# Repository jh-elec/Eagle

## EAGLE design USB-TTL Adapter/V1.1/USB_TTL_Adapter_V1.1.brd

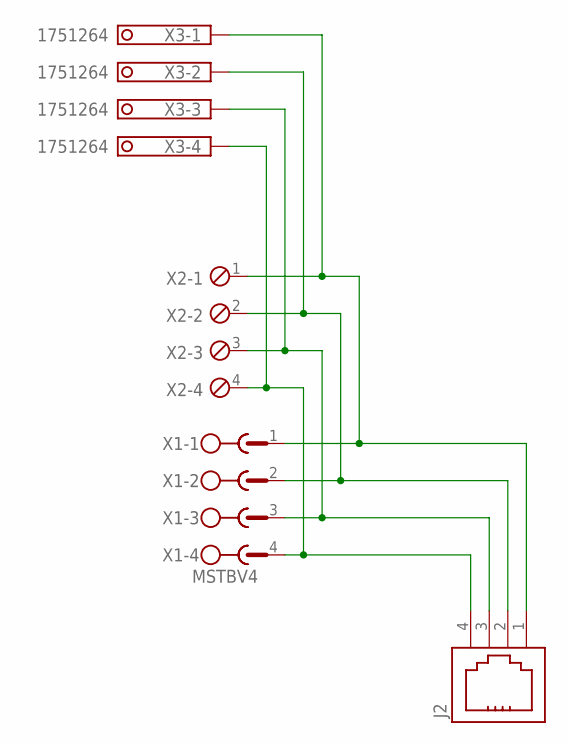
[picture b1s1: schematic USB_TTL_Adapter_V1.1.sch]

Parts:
J2: 615004144021
X1: MSTBV4
X2: MPT4; 4POL254
X3: 1751264

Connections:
unnamed: J2.4, X1.4, X2.4, X3.4
unnamed: J2.3, X1.3, X2.3, X3.3
unnamed: J2.2, X1.2, X2.2, X3.2
unnamed: J2.1, X1.1, X2.1, X3.1

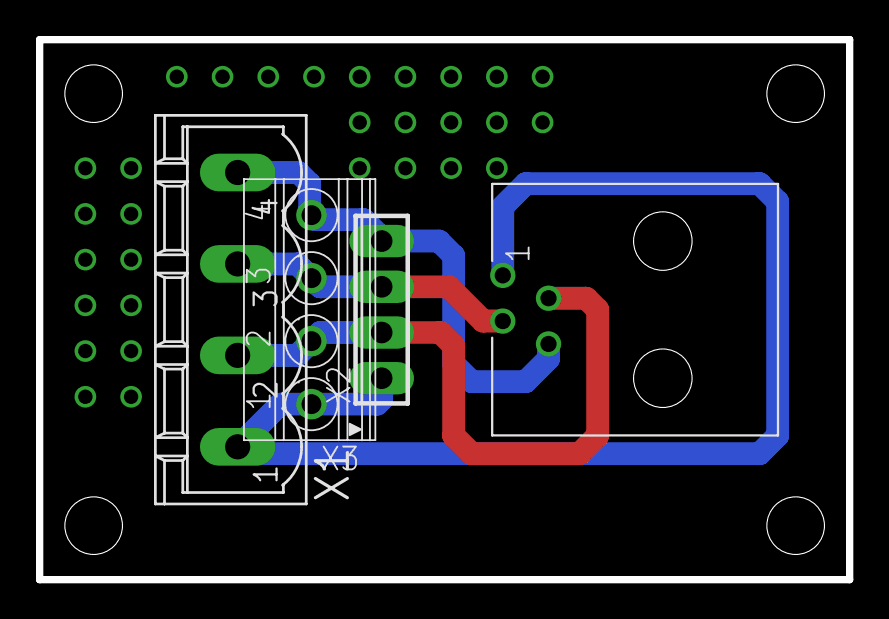
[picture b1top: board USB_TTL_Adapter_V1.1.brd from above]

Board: 2 copper layers, 45.0 x 30.0 mm, 5 parts (0 on the bottom side), 4 nets.

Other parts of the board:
U$1: 25X25_BEST

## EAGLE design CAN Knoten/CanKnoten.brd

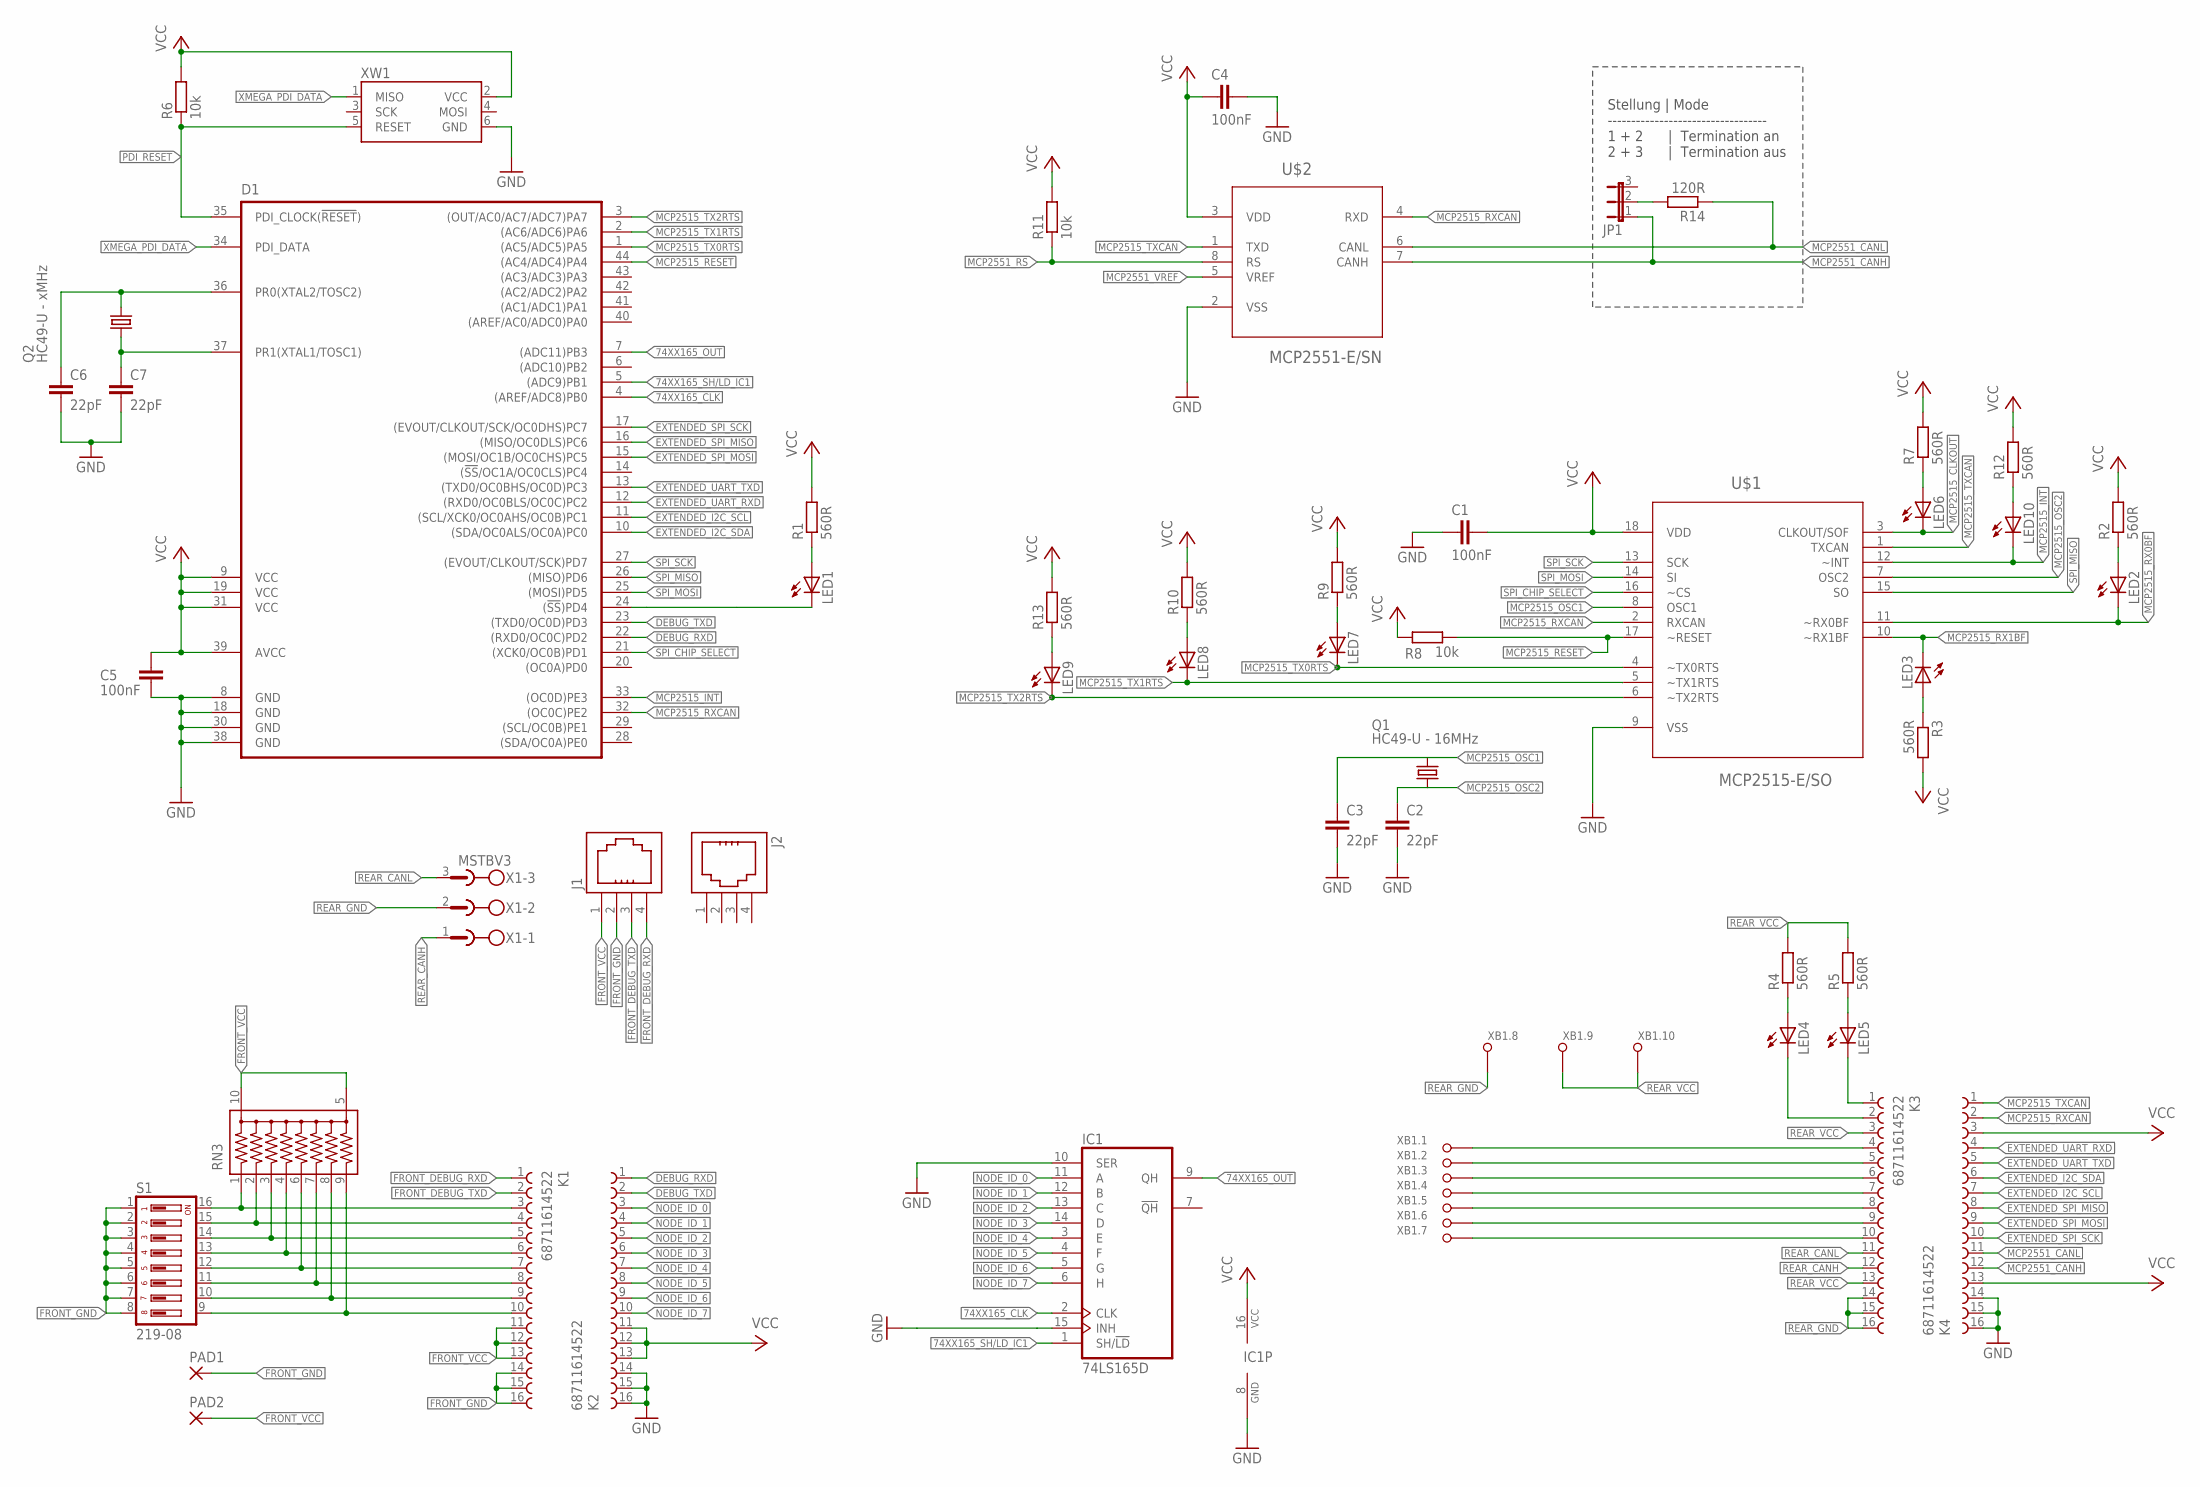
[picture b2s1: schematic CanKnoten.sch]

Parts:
C1, C4, C5: 100nF; C1206
C2, C3, C6, C7: 22pF; C1206
D1: ATXMEGA16D4/32D4/64D4/128D4-A; TQFP44A
IC1: 74LS165D; SO16
J1: 615004143821
J2: 615004144021
JP1: JP2E; JP2
K1, K2, K3, K4: 68711614522
LED1, LED2, LED3, LED4, LED5, LED6, LED7, LED8, LED9, LED10: LEDSML1206; SML1206
PAD1, PAD2: SMD5; SMD2,54-5,08
Q1: HC49-U - 16MHz; HC49
Q2: HC49-U - xMHz; HC49
R1, R2, R3, R4, R5, R7, R9, R10, R12, R13: 560R; R1206
R6, R8, R11: 10k; R1206
R14: 120R; R1206
RN3: 745-10
S1: 219-08; CTS-219-08
U$1: MCP2515-E/SO; SOIC127P1030X265-18N
U$2: MCP2551-E/SN; SOIC127P600X175-8N
X1: MSTBV3
XB1: WSL10
XW1: WSL6; WSL

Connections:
74XX165_CLK: D1.4 ((AREF/ADC8)PB0), IC1.2 (CLK)
74XX165_OUT: D1.7 ((ADC11)PB3), IC1.9 (QH)
74XX165_SH/LD_IC1: D1.5 ((ADC9)PB1), IC1.1 (SH/!LD)
DEBUG_RXD: D1.22 ((RXD0/OC0C)PD2), K2.1
DEBUG_TXD: D1.23 ((TXD0/OC0D)PD3), K2.2
EXTENDED_I2C_SCL: D1.11 ((SCL/XCK0/OC0AHS/OC0B)PC1), K4.7
EXTENDED_I2C_SDA: D1.10 ((SDA/OC0ALS/OC0A)PC0), K4.6
EXTENDED_SPI_MISO: D1.16 ((MISO/OC0DLS)PC6), K4.8
EXTENDED_SPI_MOSI: D1.15 ((MOSI/OC1B/OC0CHS)PC5), K4.9
EXTENDED_SPI_SCK: D1.17 ((EVOUT/CLKOUT/SCK/OC0DHS)PC7), K4.10
EXTENDED_UART_RXD: D1.12 ((RXD0/OC0BLS/OC0C)PC2), K4.4
EXTENDED_UART_TXD: D1.13 ((TXD0/OC0BHS/OC0D)PC3), K4.5
FRONT_DEBUG_RXD: J1.4 (1), K1.1
FRONT_DEBUG_TXD: J1.3 (2), K1.2
FRONT_GND: J1.2 (3), K1.14, K1.15, K1.16, PAD1.1, S1.1, S1.2, S1.3, S1.4, S1.5, S1.6, S1.7, S1.8
FRONT_VCC: J1.1 (4), K1.11, K1.12, K1.13, PAD2.1, RN3.5, RN3.10
GND: C1.2, C2.2, C3.2, C4.1, C5.2, C6.2, C7.2, D1.8 (GND), D1.18 (GND), D1.30 (GND), D1.38 (GND), IC1.8 (GND), IC1.10 (SER), IC1.15 (INH), K2.14, K2.15, K2.16, K4.14, K4.15, K4.16, U$1.9 (VSS), U$2.2 (VSS), XW1.6 (GND)
MCP2515_CLKOUT: LED6.C, U$1.3 (CLKOUT/SOF)
MCP2515_INT: D1.33 ((OC0D)PE3), LED10.C, U$1.12 (~INT)
MCP2515_OSC1: C3.1, Q1.2, U$1.8 (OSC1)
MCP2515_OSC2: C2.1, Q1.1, U$1.7 (OSC2)
MCP2515_RESET: D1.44 ((AC4/ADC4)PA4), R8.1, U$1.17 (~RESET)
MCP2515_RX0BF: LED2.C, U$1.11 (~RX0BF)
MCP2515_RX1BF: LED3.C, U$1.10 (~RX1BF)
MCP2515_RXCAN: D1.32 ((OC0C)PE2), K4.2, U$1.2 (RXCAN), U$2.4 (RXD)
MCP2515_TX0RTS: D1.1 ((AC5/ADC5)PA5), LED7.C, U$1.4 (~TX0RTS)
MCP2515_TX1RTS: D1.2 ((AC6/ADC6)PA6), LED8.C, U$1.5 (~TX1RTS)
MCP2515_TX2RTS: D1.3 ((OUT/AC0/AC7/ADC7)PA7), LED9.C, U$1.6 (~TX2RTS)
MCP2515_TXCAN: K4.1, U$1.1 (TXCAN), U$2.1 (TXD)
MCP2551_CANH: JP1.1, K4.12, U$2.7 (CANH)
MCP2551_CANL: K4.11, R14.1, U$2.6 (CANL)
MCP2551_RS: R11.1, U$2.8 (RS)
MCP2551_VREF: U$2.5 (VREF)
unnamed: LED2.A, R2.1
unnamed: K3.4, XB1.1
unnamed: LED3.A, R3.1
unnamed: K3.5, XB1.2
unnamed: K3.6, XB1.3
unnamed: K3.7, XB1.4
unnamed: K3.8, XB1.5
unnamed: K3.9, XB1.6
unnamed: K3.10, XB1.7
unnamed: LED10.A, R12.1
unnamed: JP1.2, R14.2
unnamed: LED6.A, R7.1
unnamed: LED7.A, R9.1
unnamed: C6.1, D1.36 (PR0(XTAL2/TOSC2)), Q2.2
unnamed: C7.1, D1.37 (PR1(XTAL1/TOSC1)), Q2.1
unnamed: LED8.A, R10.1
unnamed: LED9.A, R13.1
unnamed: K1.3, RN3.1, S1.16
unnamed: K1.4, RN3.2, S1.15
unnamed: K1.5, RN3.3, S1.14
unnamed: K1.6, RN3.4, S1.13
unnamed: K1.7, RN3.6, S1.12
unnamed: K1.8, RN3.7, S1.11
unnamed: K1.9, RN3.8, S1.10
unnamed: K1.10, RN3.9, S1.9
unnamed: LED1.A, R1.1
unnamed: LED4.A, R4.1
unnamed: LED5.A, R5.1
NODE_ID_0: IC1.11 (A), K2.3
NODE_ID_1: IC1.12 (B), K2.4
NODE_ID_2: IC1.13 (C), K2.5
NODE_ID_3: IC1.14 (D), K2.6
NODE_ID_4: IC1.3 (E), K2.7
NODE_ID_5: IC1.4 (F), K2.8
NODE_ID_6: IC1.5 (G), K2.9
NODE_ID_7: IC1.6 (H), K2.10
PDI_RESET: D1.35 (PDI_CLOCK(!RESET!)), R6.1, XW1.5 (RESET)
REAR_CANH: K3.12, X1.1
REAR_CANL: K3.11, X1.3
REAR_GND: K3.14, K3.15, K3.16, X1.2, XB1.8
REAR_MCP2515_RXCAN: K3.2, LED4.C
REAR_MCP2515_TXCAN: K3.1, LED5.C
REAR_VCC: K3.3, K3.13, R4.2, R5.2, XB1.9, XB1.10
SPI_CHIP_SELECT: D1.21 ((XCK0/OC0B)PD1), U$1.16 (~CS)
SPI_MISO: D1.26 ((MISO)PD6), U$1.15 (SO)
SPI_MOSI: D1.25 ((MOSI)PD5), U$1.14 (SI)
SPI_SCK: D1.27 ((EVOUT/CLKOUT/SCK)PD7), U$1.13 (SCK)
SPI_SLAVE_SELECT_HW: D1.24 ((!SS!)PD4), LED1.C
VCC: C1.1, C4.2, C5.1, D1.9 (VCC), D1.19 (VCC), D1.31 (VCC), D1.39 (AVCC), IC1.16 (VCC), K2.11, K2.12, K2.13, K4.3, K4.13, R1.2, R2.2, R3.2, R6.2, R7.2, R8.2, R9.2, R10.2, R11.2, R12.2, R13.2, U$1.18 (VDD), U$2.3 (VDD), XW1.2 (VCC)
XMEGA_PDI_DATA: D1.34 (PDI_DATA), XW1.1 (MISO)

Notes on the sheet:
Stellung | Mode ---------------------------------- 1 + 2 | Termination an 2 + 3 | Termination aus

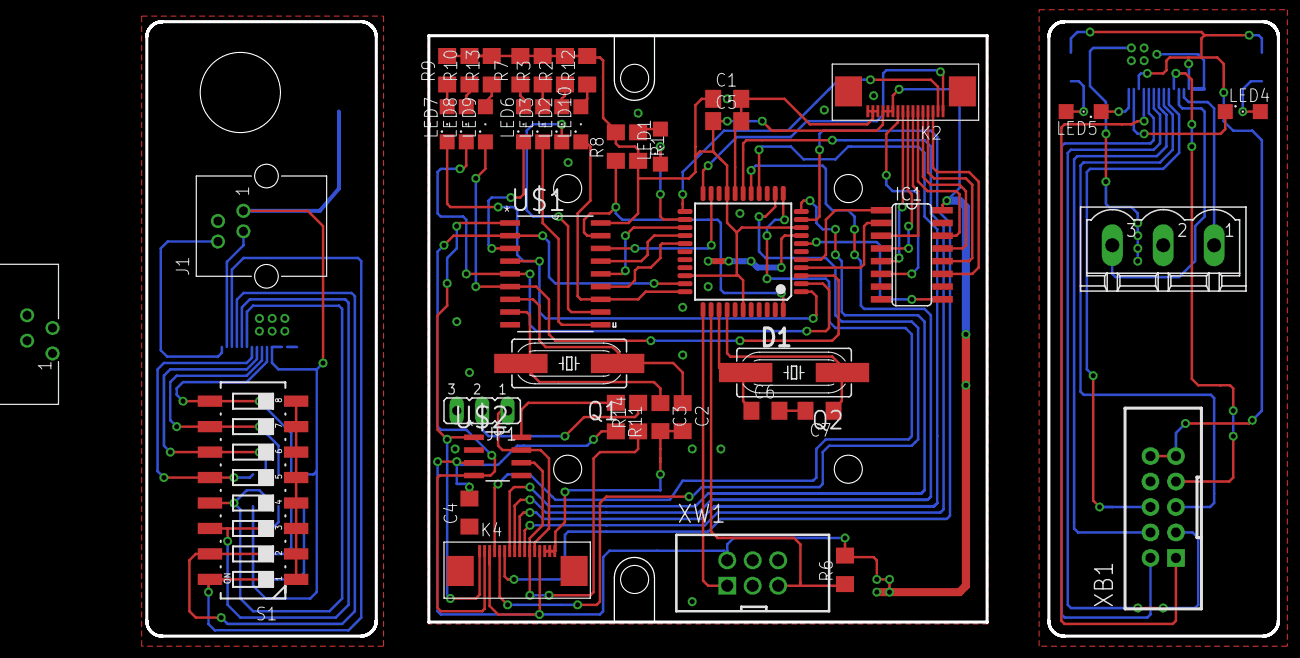
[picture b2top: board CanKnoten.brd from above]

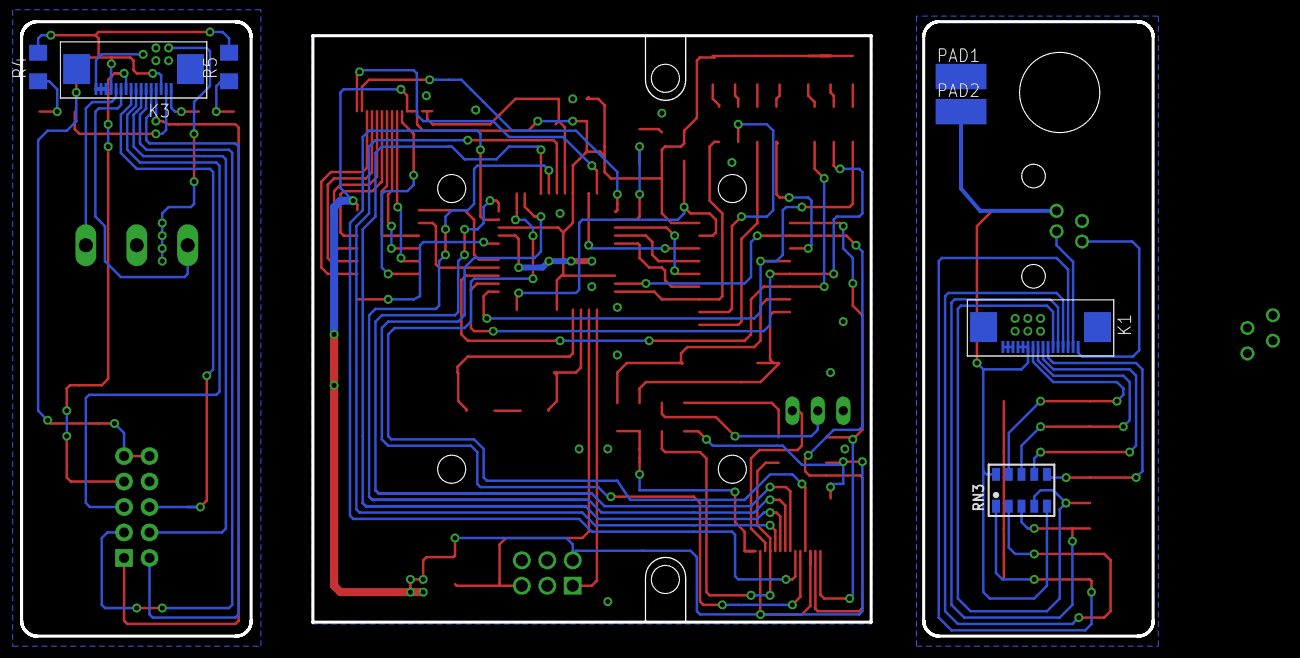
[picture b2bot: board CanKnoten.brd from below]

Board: 2 copper layers, 112.9 x 61.3 mm, 53 parts (7 on the bottom side), 82 nets.

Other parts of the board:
U$3: RND_455-00879_X4
U$4: 25X25_BEST

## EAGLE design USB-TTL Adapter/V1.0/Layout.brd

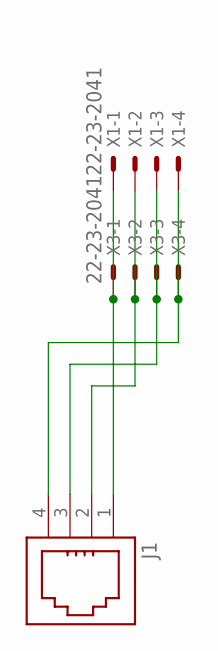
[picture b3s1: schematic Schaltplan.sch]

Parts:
J1: 615004143821
X1, X3: 22-23-2041

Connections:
unnamed: J1.1 (4), X1.1, X3.1
unnamed: J1.2 (3), X1.2, X3.2
unnamed: J1.3 (2), X1.3, X3.3
unnamed: J1.4 (1), X1.4, X3.4

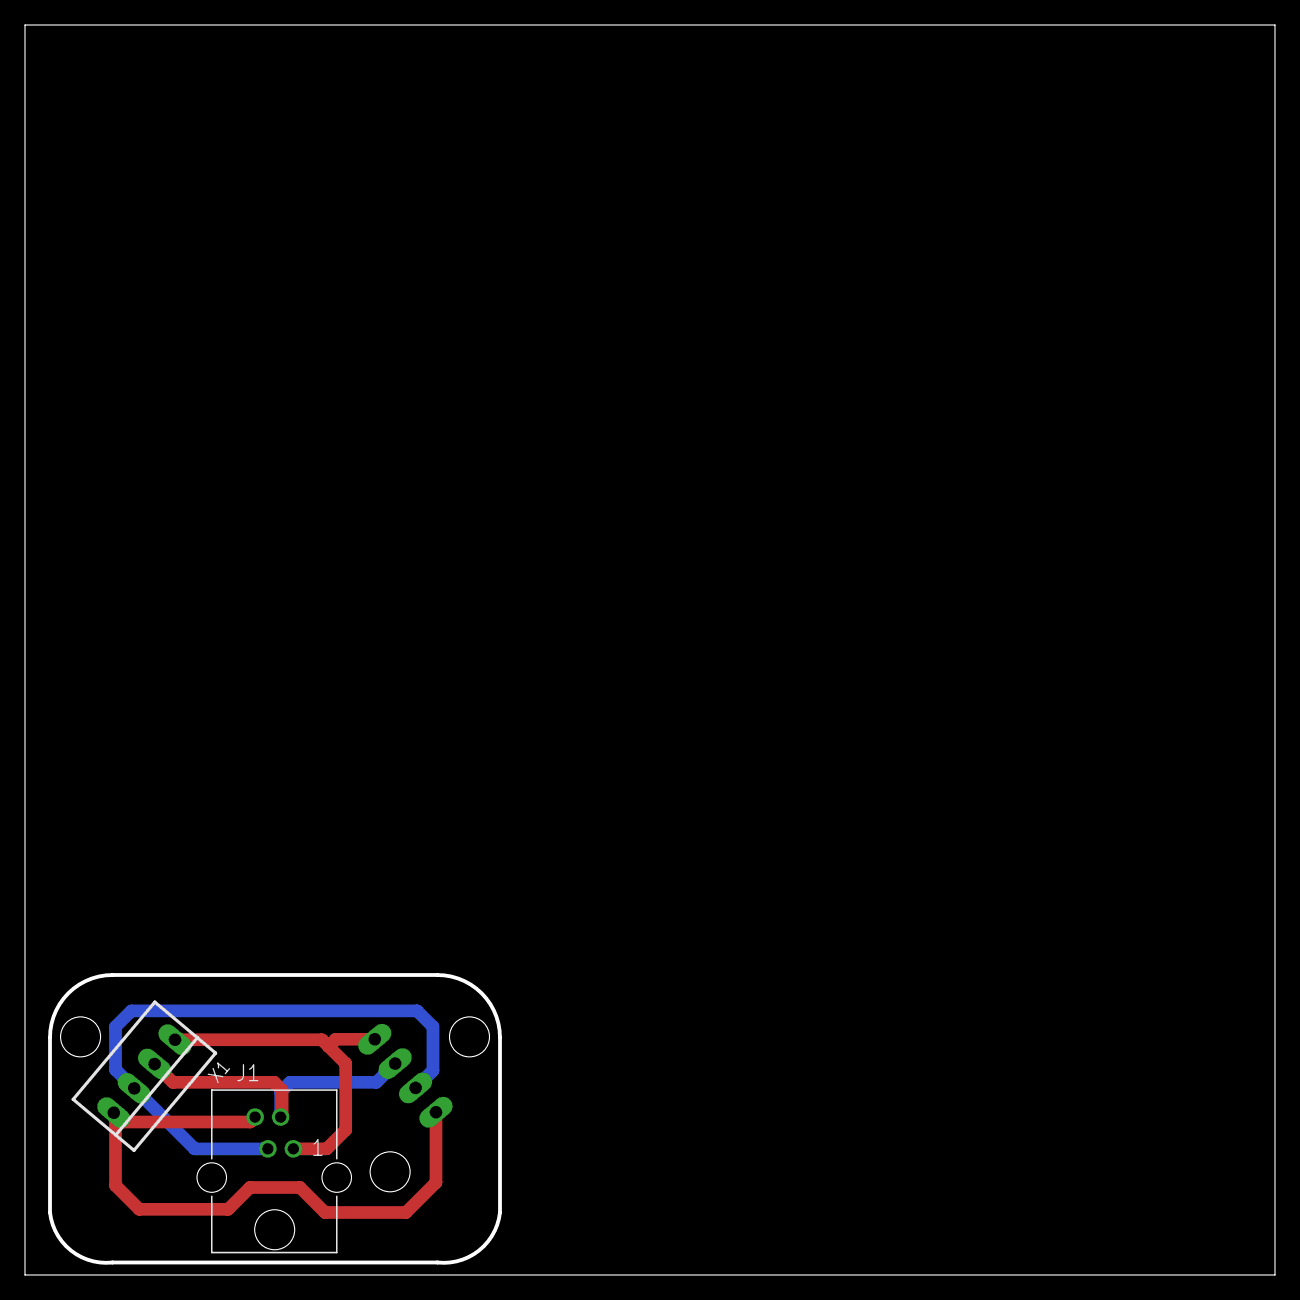
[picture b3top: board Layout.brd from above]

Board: 2 copper layers, 100.0 x 100.0 mm, 4 parts (1 on the bottom side), 4 nets.

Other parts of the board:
E$1: 25X25_BEST

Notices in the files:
parts and their libraries:
InputOutputIO: Copyright: Würth Elektronik
resistor-array: Copyright (C) 2008, Bob Starr
